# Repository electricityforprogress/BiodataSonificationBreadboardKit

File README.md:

# BiodataSonificationBreadboardKit
Biodata Sonification kit using breadboard, for Arduino Uno 'Sheild'

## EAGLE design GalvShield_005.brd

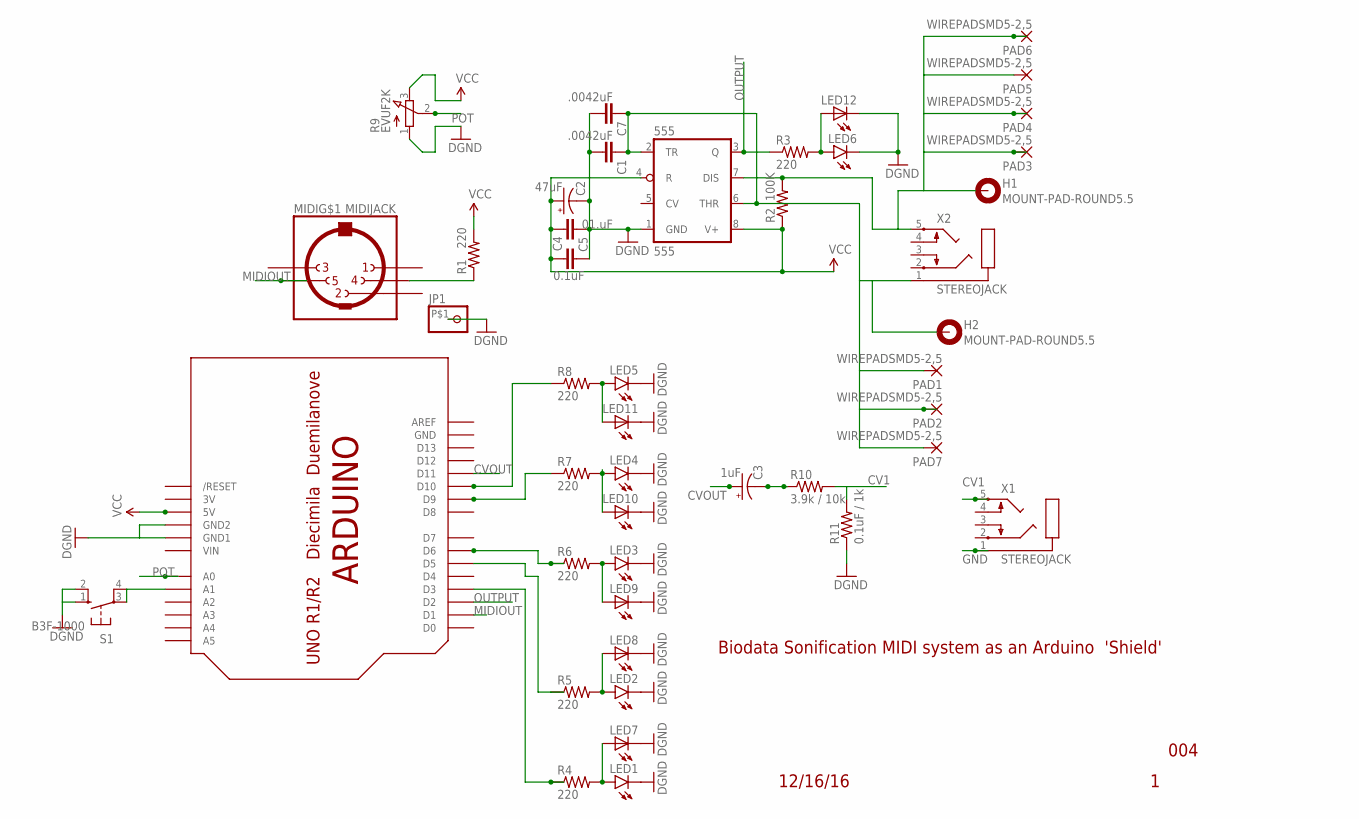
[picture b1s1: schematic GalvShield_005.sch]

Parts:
555: 555; DIL08-ROUND
C1: .0042uF; CAP-PTH-SMALL
C2: 47uF; CPOL-RADIAL-10UF-25V
C3: 1uF; CPOL-RADIAL-10UF-25V
C4: 0.1uF; CAP-PTH-SMALL
C5: 01.uF; 1206
C7: .0042uF; 1206
H1, H2: MOUNT-PAD-ROUND5.5; 5,5-PAD
JP1: PINHD-1X1-BIGPOGO; 1X1-BIGPOGO
LED1, LED2, LED3, LED4, LED5, LED6: LED5MM
LED7, LED8, LED9, LED10, LED11, LED12: LEDSML1206; SML1206
MIDI: MIDIJACK; CP-2350
PAD1, PAD2, PAD3, PAD4, PAD5, PAD6, PAD7: WIREPADSMD5-2,5; 5-2,5
R1, R3, R4, R5, R6, R7, R8: 220; 0805-THM-7
R2: 100K; 0805-THM-7
R9: EVUF2K; EVUFXK
R10: 3.9k / 10k; 0805-THM-7
R11: 0.1uF / 1k; 0805-THM-7
S1: B3F-1000; B3F-10XX
U$3: ARDUINOUNO; ARDUINO
X1, X2: STEREOJACK; STX3100

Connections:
3V: U$3.3V
CV1: R10.2, R11.2, X1.5
CVOUT: C3.1 (+), U$3.D11
GND: 555.1 (GND), C1.2, C2.2 (-), C4.2, C5.1, C7.2, JP1.P$1, LED1.K (C), LED2.K (C), LED3.K (C), LED4.K (C), LED5.K (C), LED6.K (C), LED7.C, LED8.C, LED9.C, LED10.C, LED11.C, LED12.C, R9.1 (A), R11.1, S1.1 (S), S1.2 (S1), U$3.GND, U$3.GND1, U$3.GND2, X1.1
MIDIOUT: MIDI.5, U$3.D1
unnamed: C3.2 (-), R10.1
unnamed: S1.3, S1.4 (P1), U$3.A1
unnamed: R8.1, U$3.D10
unnamed: R4.1, U$3.D3
unnamed: R5.1, U$3.D5
unnamed: MIDI.4, R1.1
unnamed: R7.1, U$3.D9
unnamed: R6.1, U$3.D6
unnamed: LED1.A, LED7.A, R4.2
unnamed: LED2.A, LED8.A, R5.2
unnamed: LED3.A, LED9.A, R6.2
unnamed: LED4.A, LED10.A, R7.2
unnamed: LED5.A, LED11.A, R8.2
unnamed: LED6.A, LED12.A, R3.2
OUTPUT: 555.3 (Q), R3.1, U$3.D2
POT: R9.2 (S), U$3.A0
PROBE1: 555.2 (TR), 555.6 (THR), C1.1, C7.1, H2.B5,5, PAD1.1, PAD2.1, PAD7.1, X2.1
PROBE2: 555.7 (DIS), H1.B5,5, PAD3.1, PAD4.1, PAD5.1, PAD6.1, R2.2, X2.5
VCC: 555.4 (R), 555.8 (V+), C2.1 (+), C4.1, C5.2, R1.2, R2.1, R9.3 (E), U$3.5V
VIN: U$3.VIN

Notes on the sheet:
12/16/16
004
Biodata Sonification MIDI system as an Arduino 'Shield'

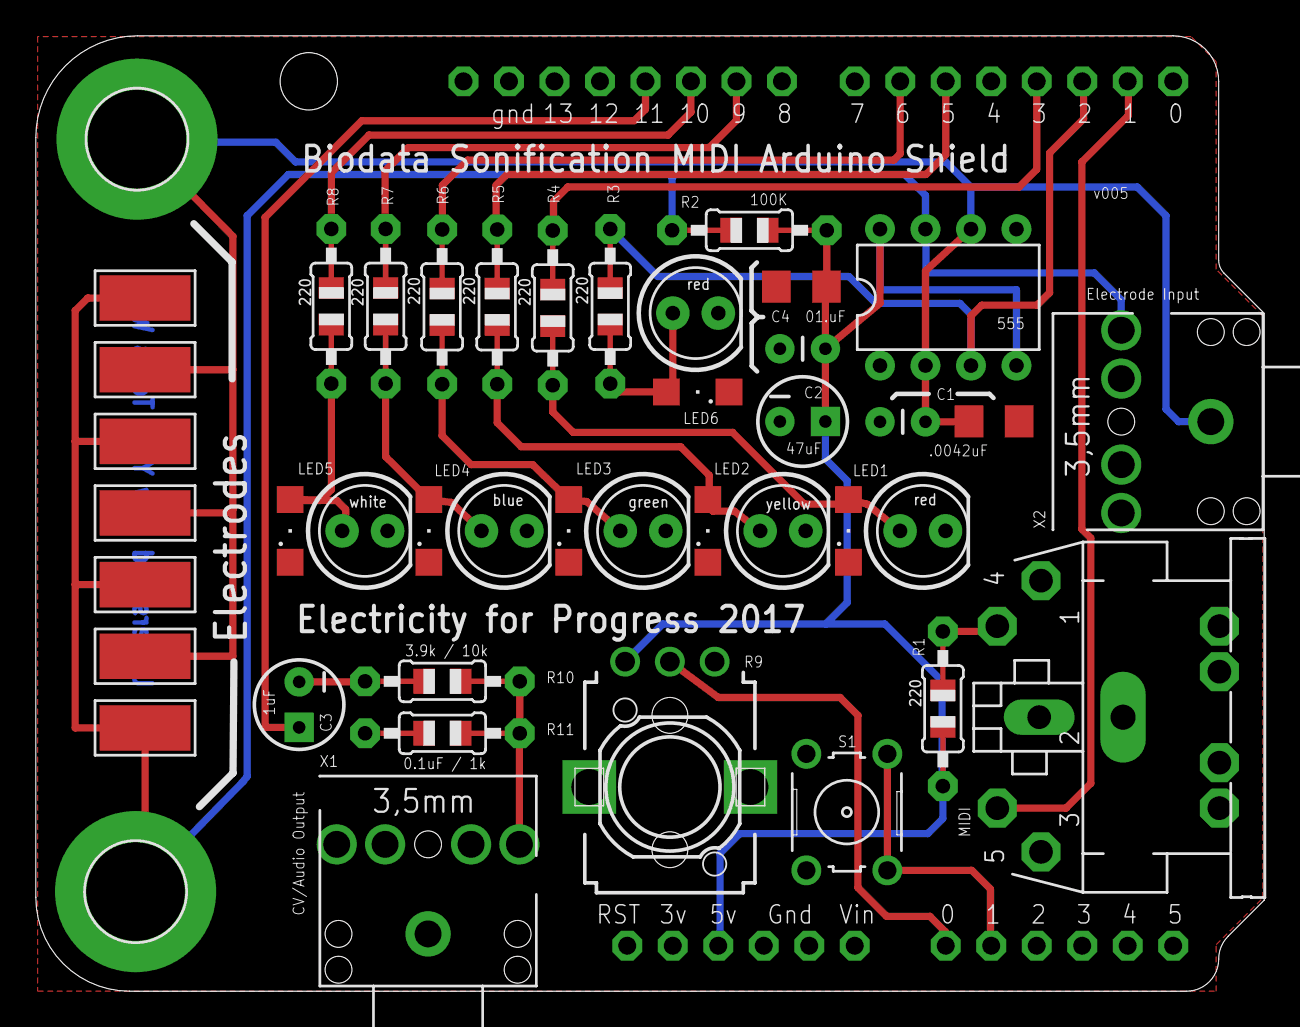
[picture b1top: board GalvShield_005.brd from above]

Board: 2 copper layers, 68.6 x 53.3 mm, 45 parts (0 on the bottom side), 23 nets.

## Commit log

2017-02-06 arduino sketch v026
    sketch update for the breadboard and arduino shield kits
2017-02-06 Kit assembly instruction guide v01
2017-02-06 Kit assembly Instructions
2017-02-07 Changes to Menu mode LED display
2017-02-11 Arduino Sketch with multiple tabs
2021-02-02 updated slide 9
    changed slide 9 to indicate correct row for 100k pull up resistor
2021-02-02 new version of kit instruction pdf
2021-02-16 modified 555 timer with link
2021-02-16 555 change
2022-03-07 change setNote
    i had a couple comments about the setNote and star. I looked and the MIDISprout and my new Biodata Feather do not use the star, so i have updated the code here.

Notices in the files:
parts and their libraries:
SparkFun-Passives: Licensing: Creative Commons ShareAlike 4.0 International - https://creativecommons.org/licenses/by-sa/4.0
